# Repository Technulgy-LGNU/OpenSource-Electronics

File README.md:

# Technulgy Open-Source Electronics

This repository contains circuits and borads of our robots. There is one folder for each released version.
Mechanics are designed with Autodesk EAGLE.

Autodesk EAGLE is available for free for students.

Please check subfolders for further information on each version.

## Electronics Assembly Team Faabs 2025

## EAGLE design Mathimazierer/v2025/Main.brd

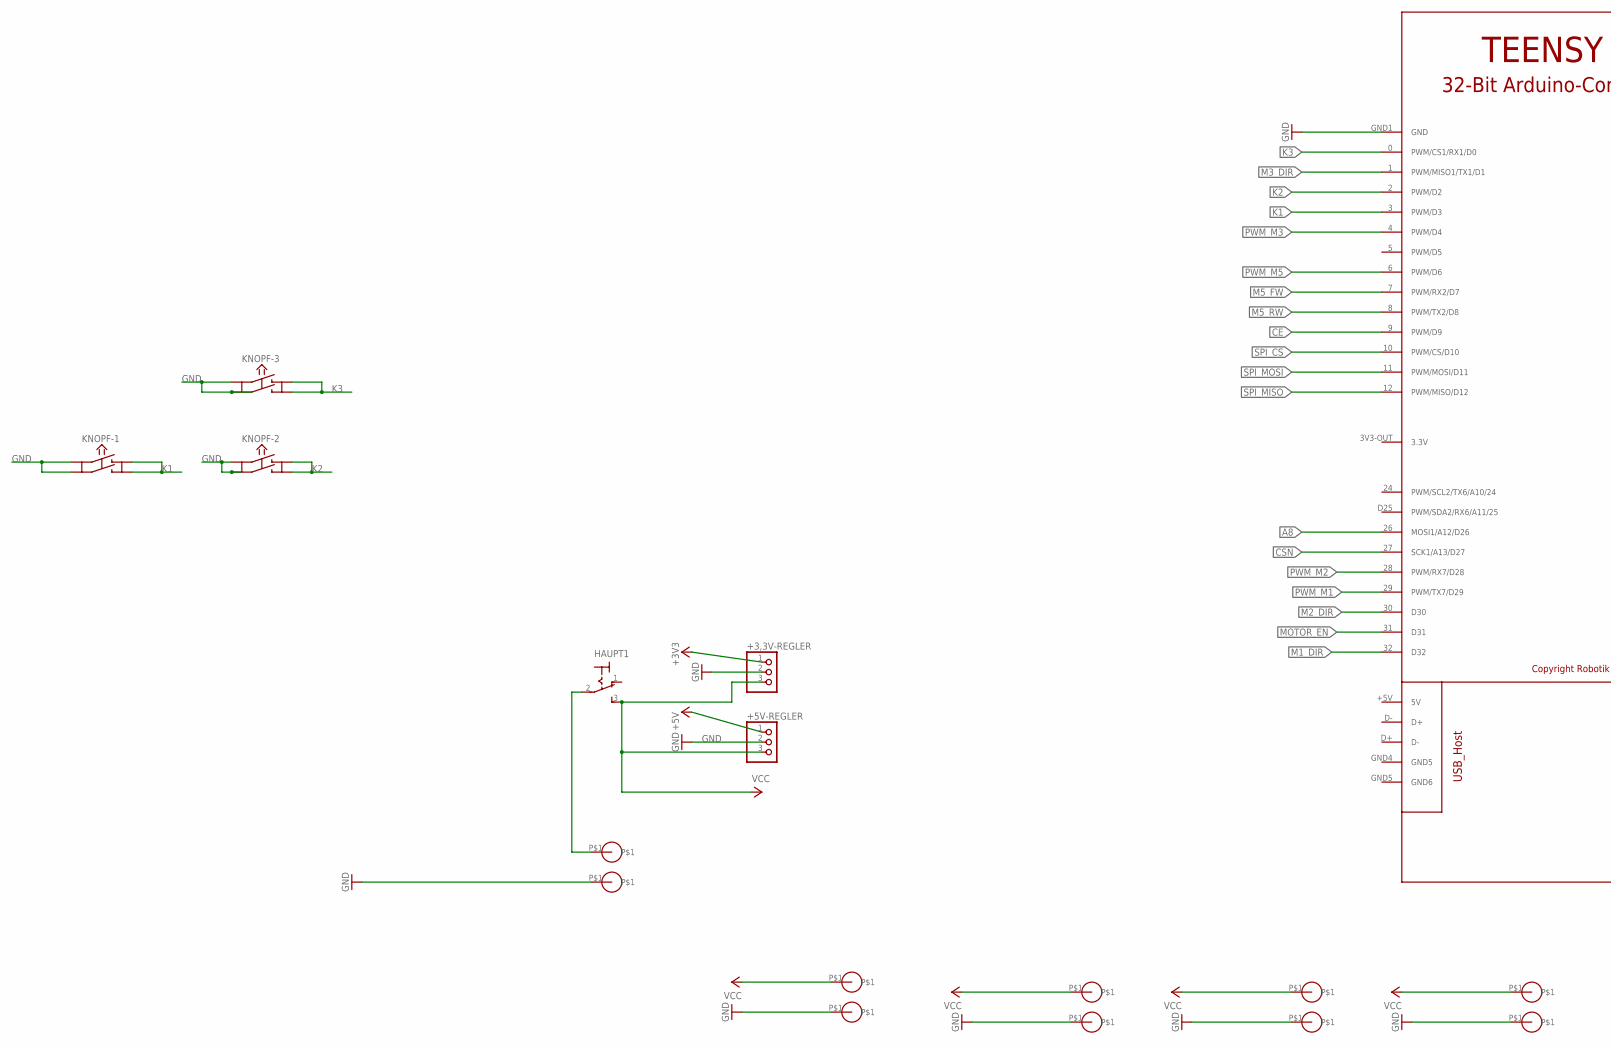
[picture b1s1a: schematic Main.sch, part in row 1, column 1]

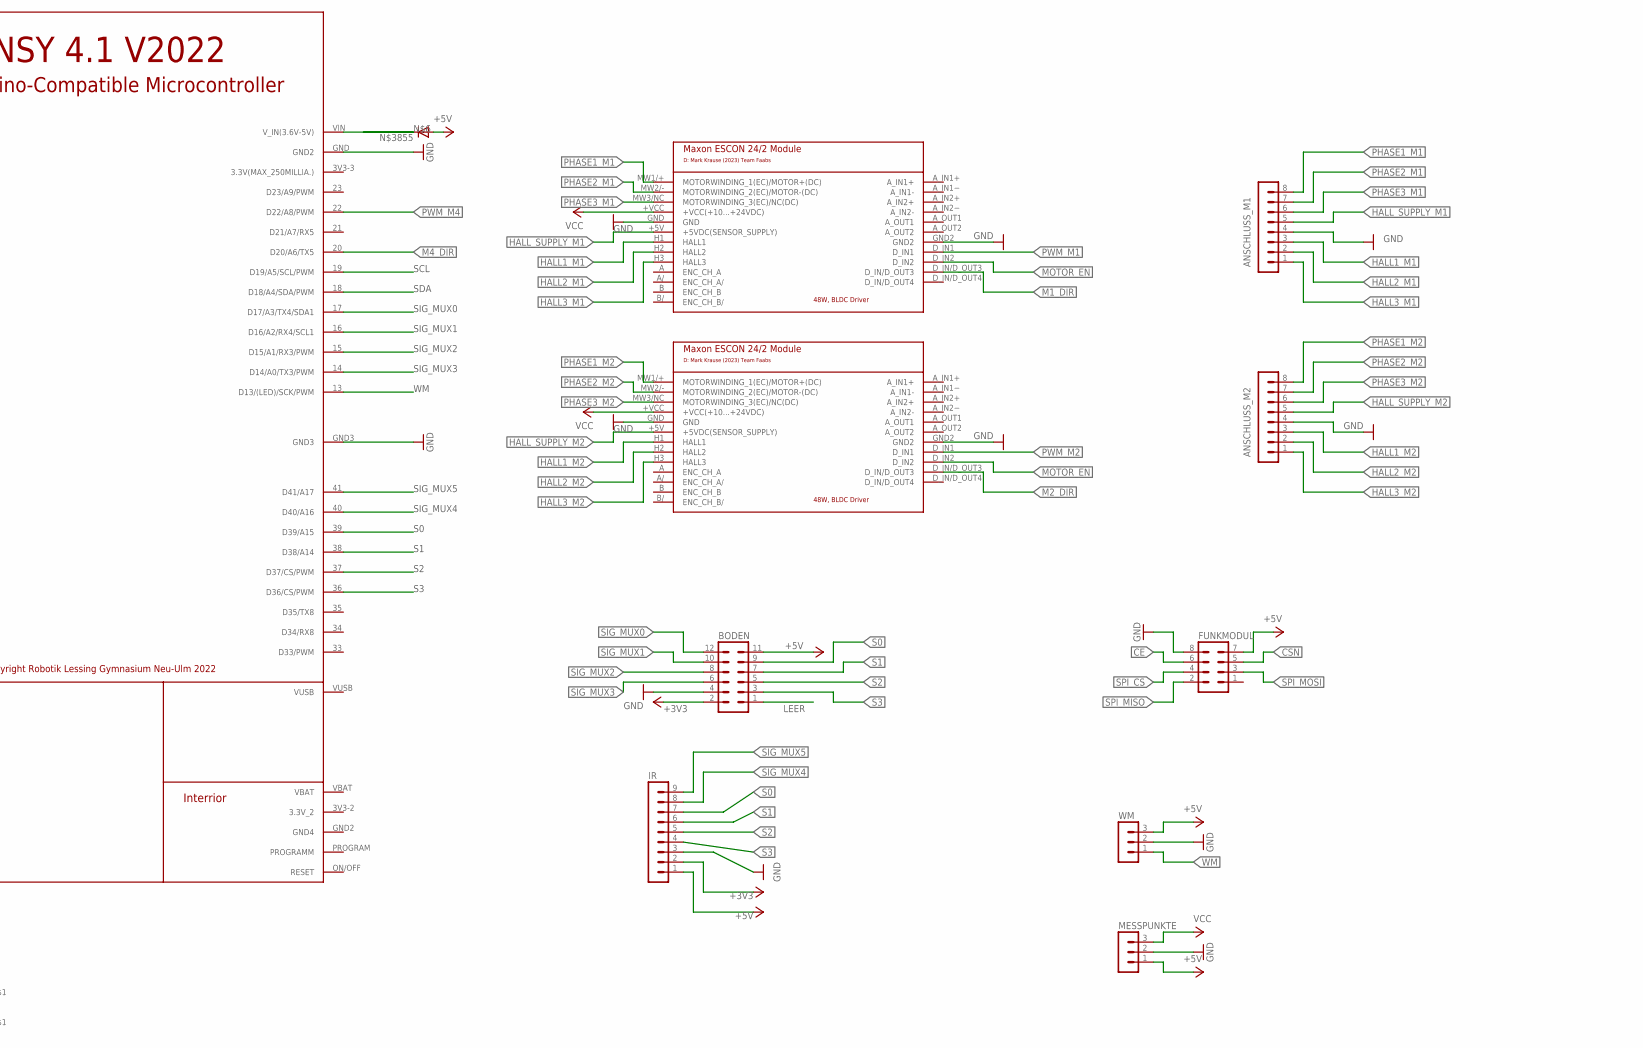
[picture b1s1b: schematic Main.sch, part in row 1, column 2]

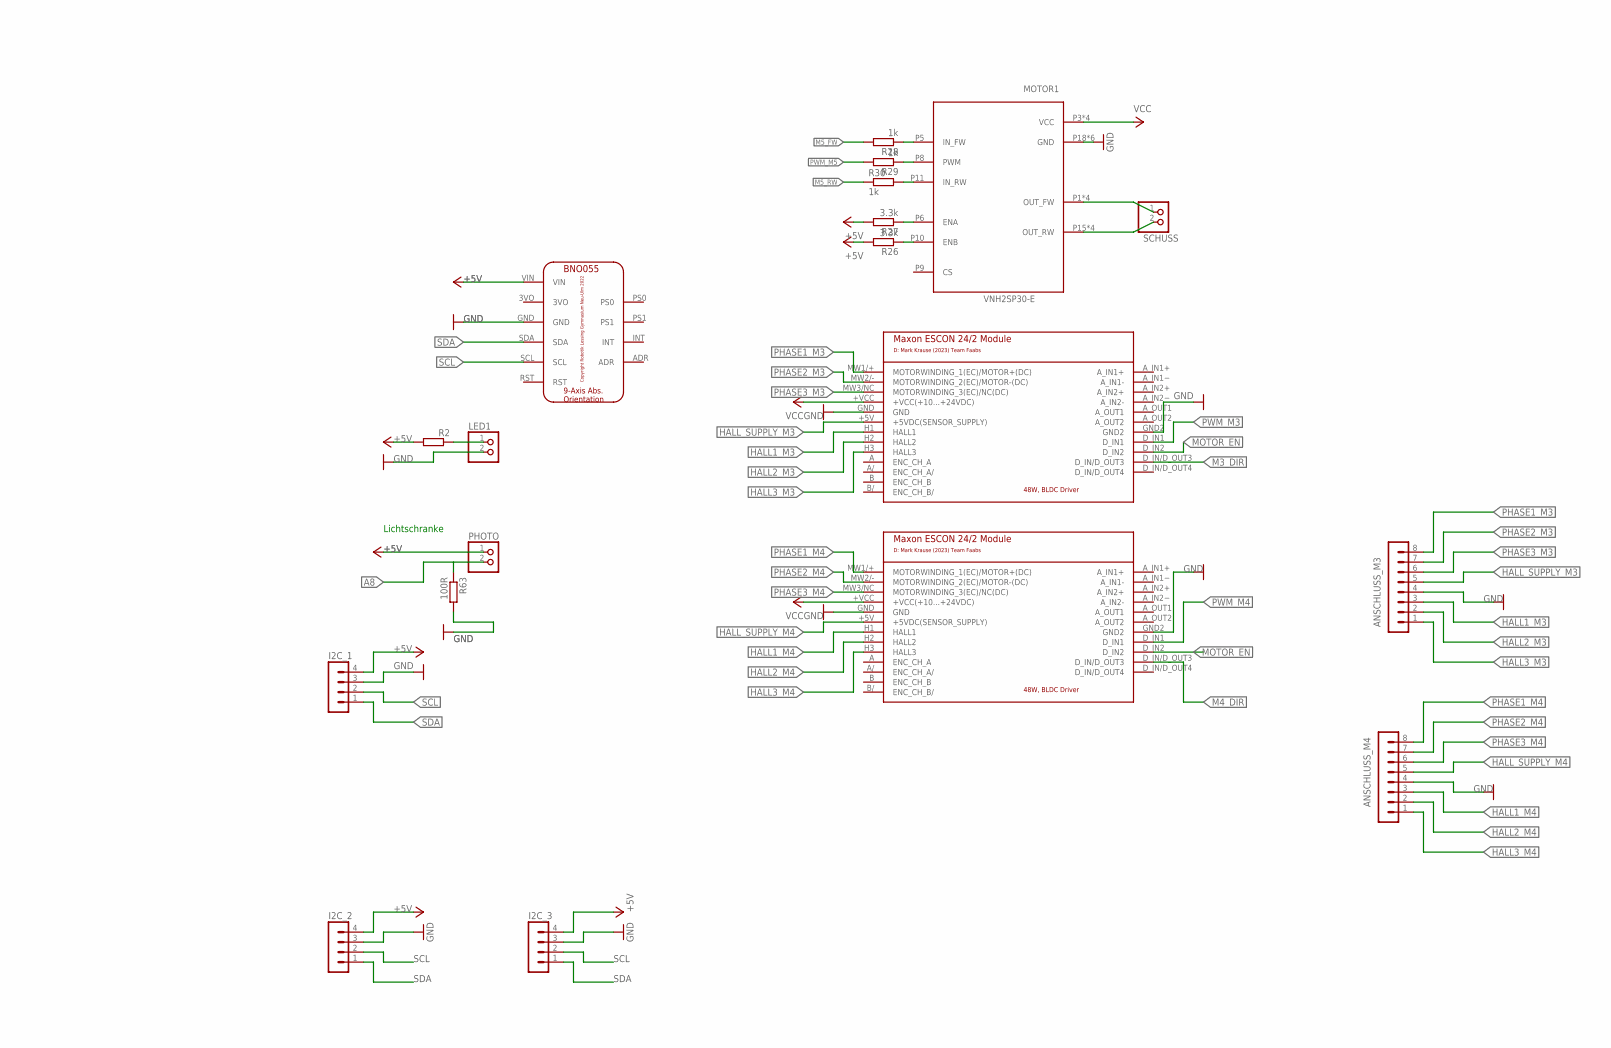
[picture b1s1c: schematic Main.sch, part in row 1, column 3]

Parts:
+3,3V-REGLER, +5V-REGLER: PINHD-1X3; 1X03
ANSCHLUSS_M1, ANSCHLUSS_M2, ANSCHLUSS_M3, ANSCHLUSS_M4: MA08-1
BNO055: BNO055
BODEN: MA06-2
FUNKMODUL: MA04-2
GND, GND10, GND11, GND35, GND37: PPAD
HAUPT1: 320-916
I2C_1, I2C_2, I2C_3: MA04-1
IR: MA09-1
KNOPF-1, KNOPF-2, KNOPF-3: KSM611A
LED1: PINHD-1X2; 1X02
MAIN, MAIN1, MAIN2, MAIN3, MAIN4: PPAD
MESSPUNKTE: MA03-1
MOTOR1: VNH2SP30-E; MP-SO-30
N$3855: DIODE-SMB; SMB
PHOTO: PINHD-1X2; 1X02
R2: 100R; R1206
R26, R27: 3.3k; R0805
R28, R29, R30: 1k; R0805
R63: 100R; R0805
SCHUSS: PINHD-1X2; 1X02
U$1, U$3, U$4, U$5: MAXON_ESCON24/2; MAXON_ESCON24/2_MODULE
U$2: TEENSY_4.1
WM: MA03-1

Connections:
+3V3: +3,3V-REGLER.1, BODEN.2, IR.2
+5V: +5V-REGLER.1, BNO055.VIN, BODEN.11, FUNKMODUL.7, I2C_1.4, I2C_2.4, I2C_3.4, IR.1, MESSPUNKTE.1, N$3855.A, PHOTO.1, R2.2, R26.2, R27.2, WM.3
A8: PHOTO.2, R63.1, U$2.26 (MOSI1/A12/D26)
CE: FUNKMODUL.6, U$2.9 (PWM/D9)
CSN: FUNKMODUL.5, U$2.27 (SCK1/A13/D27)
GND: +3,3V-REGLER.2, +5V-REGLER.2, ANSCHLUSS_M1.4, ANSCHLUSS_M2.4, ANSCHLUSS_M3.4, ANSCHLUSS_M4.4, BNO055.GND, BODEN.4, FUNKMODUL.8, GND.P$1, GND10.P$1, GND11.P$1, GND35.P$1, GND37.P$1, I2C_1.3, I2C_2.3, I2C_3.3, IR.3, KNOPF-1.A, KNOPF-1.C, KNOPF-2.A, KNOPF-2.C, KNOPF-3.A, KNOPF-3.C, LED1.2, MESSPUNKTE.2, MOTOR1.P18 (GND), MOTOR1.P19 (GND), MOTOR1.P20 (GND), MOTOR1.P26 (GND), MOTOR1.P27 (GND), MOTOR1.P28 (GND), R63.2, U$1.GND, U$1.GND2, U$2.GND (GND2), U$2.GND1 (GND), U$2.GND3, U$3.GND, U$3.GND2, U$4.GND, U$4.GND2, U$5.GND, U$5.GND2, WM.2
HALL1_M1: ANSCHLUSS_M1.3, U$1.H1 (HALL1)
HALL1_M2: ANSCHLUSS_M2.3, U$3.H1 (HALL1)
HALL1_M3: ANSCHLUSS_M3.3, U$4.H1 (HALL1)
HALL1_M4: ANSCHLUSS_M4.3, U$5.H1 (HALL1)
HALL2_M1: ANSCHLUSS_M1.2, U$1.H2 (HALL2)
HALL2_M2: ANSCHLUSS_M2.2, U$3.H2 (HALL2)
HALL2_M3: ANSCHLUSS_M3.2, U$4.H2 (HALL2)
HALL2_M4: ANSCHLUSS_M4.2, U$5.H2 (HALL2)
HALL3_M1: ANSCHLUSS_M1.1, U$1.H3 (HALL3)
HALL3_M2: ANSCHLUSS_M2.1, U$3.H3 (HALL3)
HALL3_M3: ANSCHLUSS_M3.1, U$4.H3 (HALL3)
HALL3_M4: ANSCHLUSS_M4.1, U$5.H3 (HALL3)
HALL_SUPPLY_M1: ANSCHLUSS_M1.5, U$1.+5V (+5VDC(SENSOR_SUPPLY))
HALL_SUPPLY_M2: ANSCHLUSS_M2.5, U$3.+5V (+5VDC(SENSOR_SUPPLY))
HALL_SUPPLY_M3: ANSCHLUSS_M3.5, U$4.+5V (+5VDC(SENSOR_SUPPLY))
HALL_SUPPLY_M4: ANSCHLUSS_M4.5, U$5.+5V (+5VDC(SENSOR_SUPPLY))
K1: KNOPF-1.B, KNOPF-1.D, U$2.3 (PWM/D3)
K2: KNOPF-2.B, KNOPF-2.D, U$2.2 (PWM/D2)
K3: KNOPF-3.B, KNOPF-3.D, U$2.0 (PWM/CS1/RX1/D0)
LEER: BODEN.1
M1_DIR: U$1.D_IN/D_OUT3, U$2.32 (D32)
M2_DIR: U$2.30 (D30), U$3.D_IN/D_OUT3
M3_DIR: U$2.1 (PWM/MISO1/TX1/D1), U$4.D_IN/D_OUT3
M4_DIR: U$2.20 (D20/A6/TX5), U$5.D_IN/D_OUT3
M5_FW: R28.2, U$2.7 (PWM/RX2/D7)
M5_RW: R30.1, U$2.8 (PWM/TX2/D8)
MOTOR_EN: U$1.D_IN2, U$2.31 (D31), U$3.D_IN2, U$4.D_IN2, U$5.D_IN2
unnamed: HAUPT1.2, MAIN.P$1
unnamed: LED1.1, R2.1
unnamed: N$3855.C, U$2.VIN (V_IN(3.6V-5V))
unnamed: MOTOR1.P5 (IN_FW), R28.1
unnamed: MOTOR1.P6 (ENA), R27.1
unnamed: MOTOR1.P10 (ENB), R26.1
unnamed: MOTOR1.P8 (PWM), R29.1
unnamed: MOTOR1.P11 (IN_RW), R30.2
unnamed: MOTOR1.P1 (OUT_FW), MOTOR1.P25 (OUT_FW), MOTOR1.P30 (OUT_FW), MOTOR1.S2 (OUT_FW), SCHUSS.1
unnamed: MOTOR1.P15 (OUT_RW), MOTOR1.P16 (OUT_RW), MOTOR1.P21 (OUT_RW), MOTOR1.S3 (OUT_RW), SCHUSS.2
PHASE1_M1: ANSCHLUSS_M1.8, U$1.MW1/+ (MOTORWINDING_1(EC)/MOTOR+(DC))
PHASE1_M2: ANSCHLUSS_M2.8, U$3.MW1/+ (MOTORWINDING_1(EC)/MOTOR+(DC))
PHASE1_M3: ANSCHLUSS_M3.8, U$4.MW1/+ (MOTORWINDING_1(EC)/MOTOR+(DC))
PHASE1_M4: ANSCHLUSS_M4.8, U$5.MW1/+ (MOTORWINDING_1(EC)/MOTOR+(DC))
PHASE2_M1: ANSCHLUSS_M1.7, U$1.MW2/- (MOTORWINDING_2(EC)/MOTOR-(DC))
PHASE2_M2: ANSCHLUSS_M2.7, U$3.MW2/- (MOTORWINDING_2(EC)/MOTOR-(DC))
PHASE2_M3: ANSCHLUSS_M3.7, U$4.MW2/- (MOTORWINDING_2(EC)/MOTOR-(DC))
PHASE2_M4: ANSCHLUSS_M4.7, U$5.MW2/- (MOTORWINDING_2(EC)/MOTOR-(DC))
PHASE3_M1: ANSCHLUSS_M1.6, U$1.MW3/NC (MOTORWINDING_3(EC)/NC(DC))
PHASE3_M2: ANSCHLUSS_M2.6, U$3.MW3/NC (MOTORWINDING_3(EC)/NC(DC))
PHASE3_M3: ANSCHLUSS_M3.6, U$4.MW3/NC (MOTORWINDING_3(EC)/NC(DC))
PHASE3_M4: ANSCHLUSS_M4.6, U$5.MW3/NC (MOTORWINDING_3(EC)/NC(DC))
PWM_M1: U$1.D_IN1, U$2.29 (PWM/TX7/D29)
PWM_M2: U$2.28 (PWM/RX7/D28), U$3.D_IN1
PWM_M3: U$2.4 (PWM/D4), U$4.D_IN1
PWM_M4: U$2.22 (D22/A8/PWM), U$5.D_IN1
PWM_M5: R29.2, U$2.6 (PWM/D6)
S0: BODEN.9, IR.7, U$2.39 (D39/A15)
S1: BODEN.7, IR.6, U$2.38 (D38/A14)
S2: BODEN.5, IR.5, U$2.37 (D37/CS/PWM)
S3: BODEN.3, IR.4, U$2.36 (D36/CS/PWM)
SCL: BNO055.SCL, I2C_1.2, I2C_2.2, I2C_3.2, U$2.19 (D19/A5/SCL/PWM)
SDA: BNO055.SDA, I2C_1.1, I2C_2.1, I2C_3.1, U$2.18 (D18/A4/SDA/PWM)
SIG_MUX0: BODEN.12, U$2.17 (D17/A3/TX4/SDA1)
SIG_MUX1: BODEN.10, U$2.16 (D16/A2/RX4/SCL1)
SIG_MUX2: BODEN.8, U$2.15 (D15/A1/RX3/PWM)
SIG_MUX3: BODEN.6, U$2.14 (D14/A0/TX3/PWM)
SIG_MUX4: IR.8, U$2.40 (D40/A16)
SIG_MUX5: IR.9, U$2.41 (D41/A17)
SPI_CS: FUNKMODUL.4, U$2.10 (PWM/CS/D10)
SPI_MISO: FUNKMODUL.2, U$2.12 (PWM/MISO/D12)
SPI_MOSI: FUNKMODUL.3, U$2.11 (PWM/MOSI/D11)
VCC: +3,3V-REGLER.3, +5V-REGLER.3, HAUPT1.3 (S), MAIN1.P$1, MAIN2.P$1, MAIN3.P$1, MAIN4.P$1, MESSPUNKTE.3, MOTOR1.P3 (VCC), MOTOR1.P13 (VCC), MOTOR1.P23 (VCC), MOTOR1.S1 (VCC), U$1.+VCC (+VCC(+10...+24VDC)), U$3.+VCC (+VCC(+10...+24VDC)), U$4.+VCC (+VCC(+10...+24VDC)), U$5.+VCC (+VCC(+10...+24VDC))
WM: U$2.13 (D13/(LED)/SCK/PWM), WM.1

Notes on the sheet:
Lichtschranke

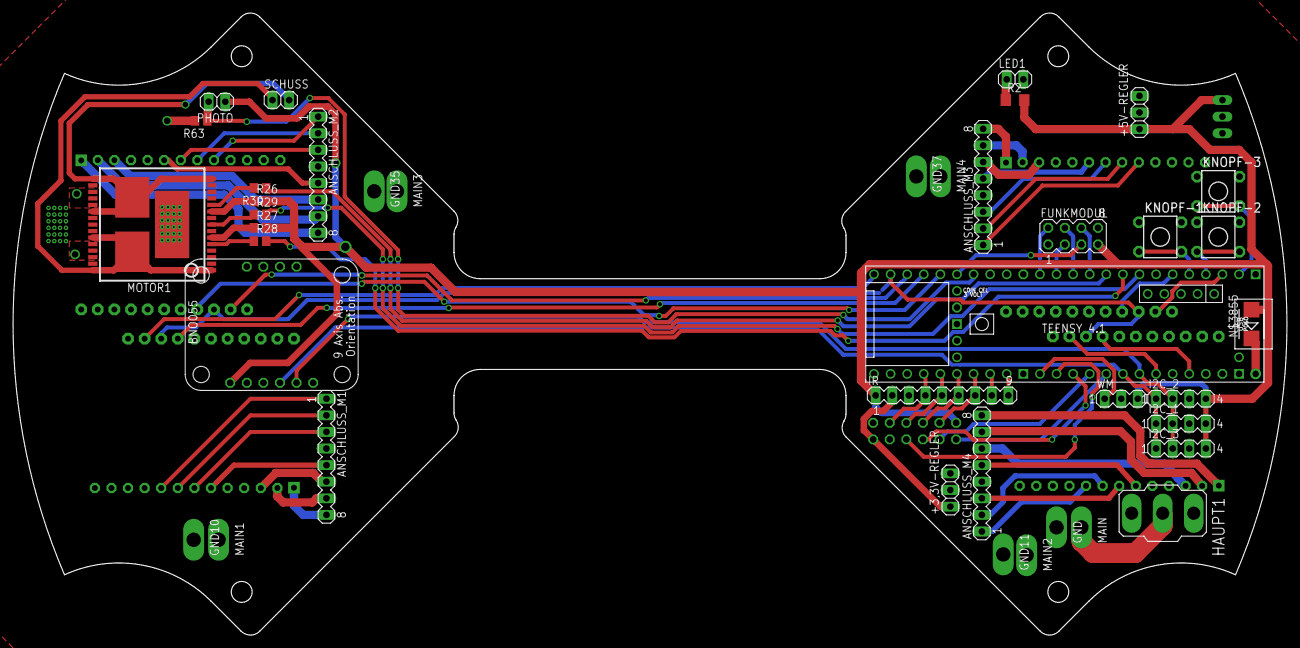
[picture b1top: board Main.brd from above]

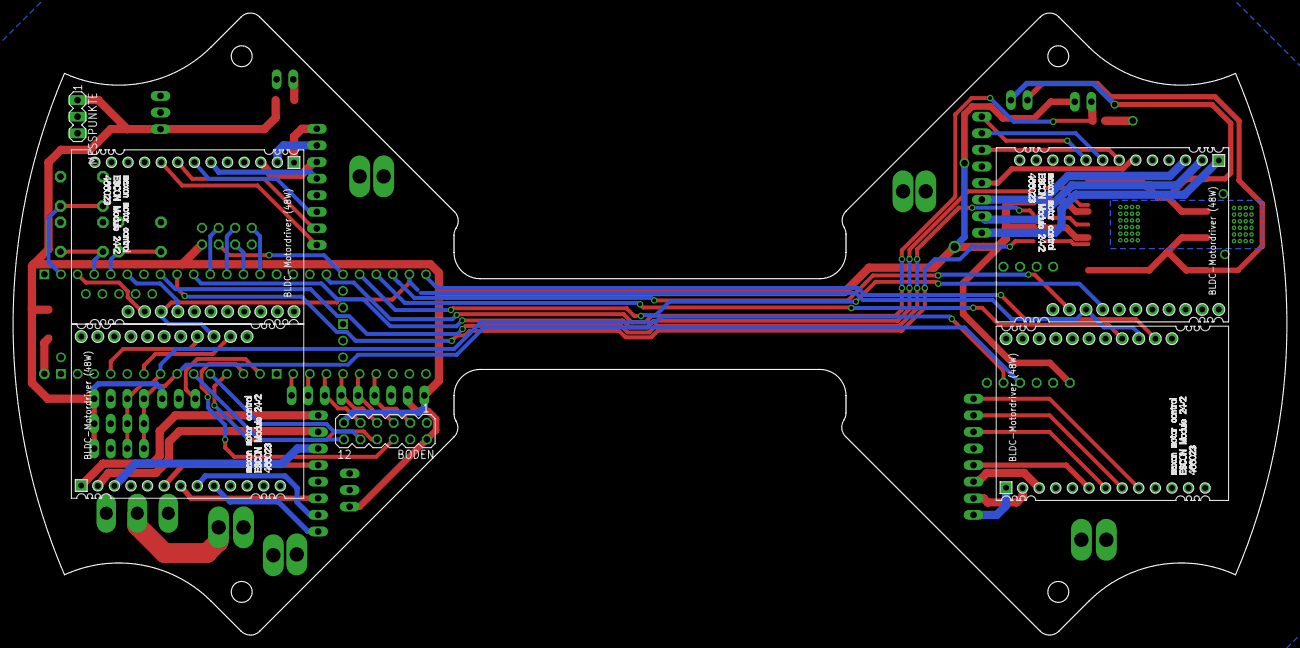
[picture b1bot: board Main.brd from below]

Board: 2 copper layers, 195.0 x 95.2 mm, 46 parts (6 on the bottom side), 76 nets.

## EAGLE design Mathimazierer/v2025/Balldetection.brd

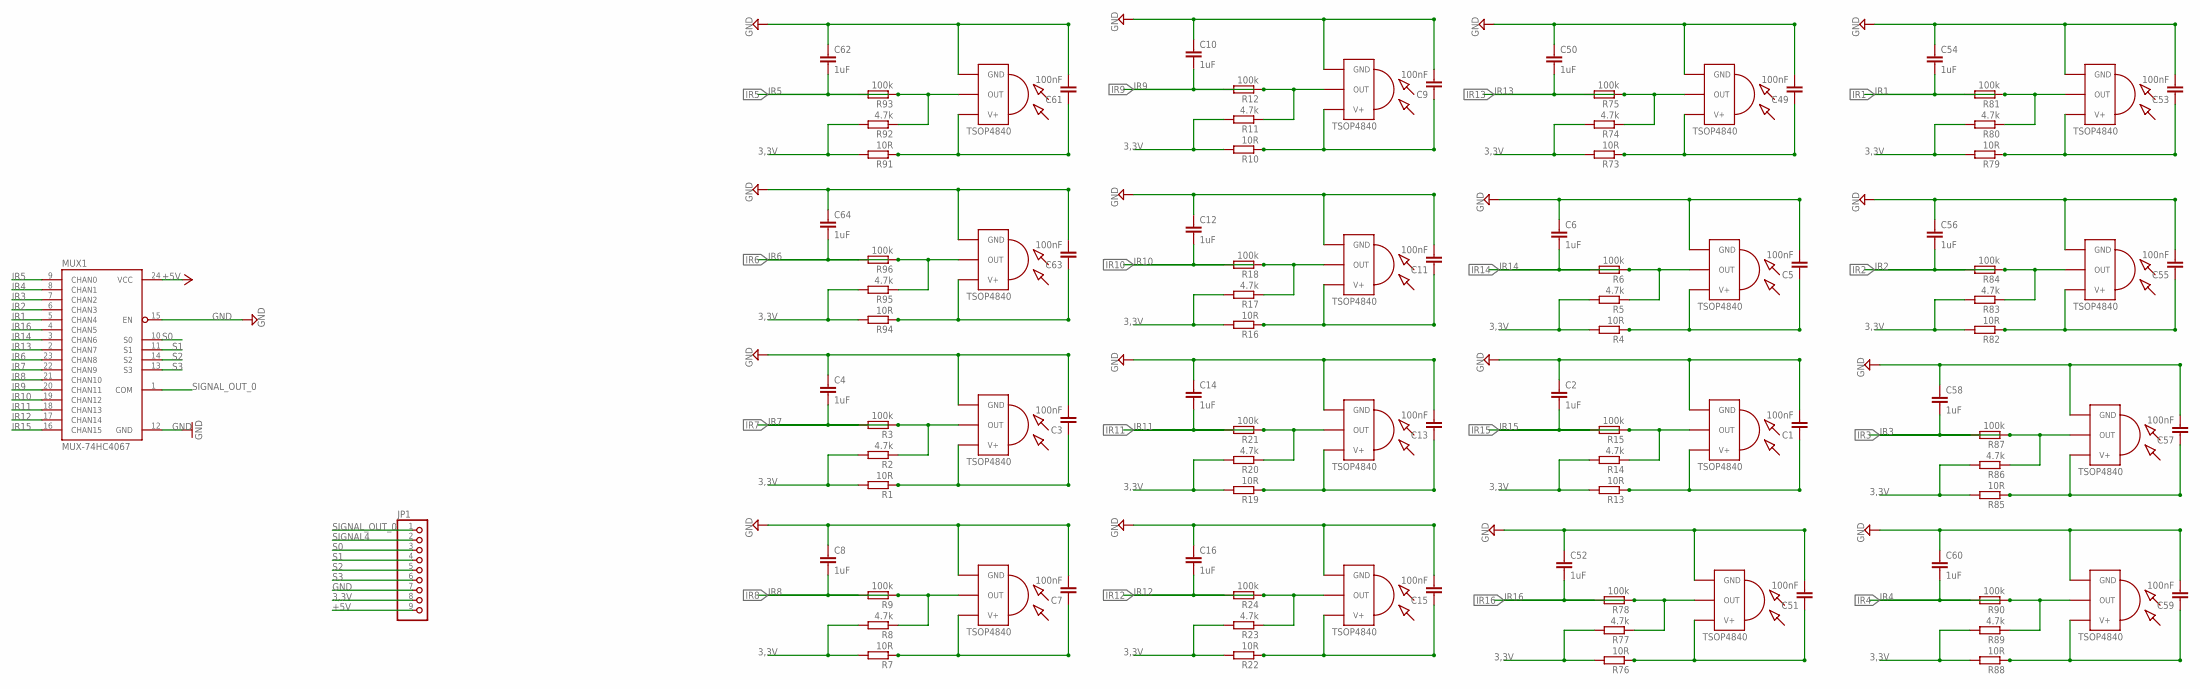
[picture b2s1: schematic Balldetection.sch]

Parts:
C1, C3, C5, C7, C9, C11, C13, C15, C49, C51, C53, C55, C57, C59, C61, C63: 100nF; C1206
C2, C4, C6, C8, C10, C12, C14, C16, C50, C52, C54, C56, C58, C60, C62, C64: 1uF; C1206
IR1, IR2, IR3, IR4, IR5, IR6, IR7, IR8, IR9, IR10, IR11, IR12, IR13, IR14, IR15, IR16: TSOP4840; TSOP18XX
JP1: PINHD-1X9; 1X09
MUX1: MUX-74HC4067; SSOP24
R1, R4, R7, R10, R13, R16, R19, R22, R73, R76, R79, R82, R85, R88, R91, R94: 10R; R1206
R2, R5, R8, R11, R14, R17, R20, R23, R74, R77, R80, R83, R86, R89, R92, R95: 4.7k; R1206
R3, R6, R9, R12, R15, R18, R21, R24, R75, R78, R81, R84, R87, R90, R93, R96: 100k; R1206

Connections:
3,3V: JP1.8, R1.2, R2.2, R4.2, R5.2, R7.2, R8.2, R10.2, R11.2, R13.2, R14.2, R16.2, R17.2, R19.2, R20.2, R22.2, R23.2, R73.2, R74.2, R76.2, R77.2, R79.2, R80.2, R82.2, R83.2, R85.2, R86.2, R88.2, R89.2, R91.2, R92.2, R94.2, R95.2
+5V: JP1.9, MUX1.24 (VCC)
GND: C1.2, C2.1, C3.2, C4.1, C5.2, C6.1, C7.2, C8.1, C9.2, C10.1, C11.2, C12.1, C13.2, C14.1, C15.2, C16.1, C49.2, C50.1, C51.2, C52.1, C53.2, C54.1, C55.2, C56.1, C57.2, C58.1, C59.2, C60.1, C61.2, C62.1, C63.2, C64.1, IR1.GND, IR2.GND, IR3.GND, IR4.GND, IR5.GND, IR6.GND, IR7.GND, IR8.GND, IR9.GND, IR10.GND, IR11.GND, IR12.GND, IR13.GND, IR14.GND, IR15.GND, IR16.GND, JP1.7, MUX1.12 (GND), MUX1.15 (EN)
IR1: C54.2, MUX1.5 (CHAN4), R81.2
IR2: C56.2, MUX1.6 (CHAN3), R84.2
IR3: C58.2, MUX1.7 (CHAN2), R87.2
IR4: C60.2, MUX1.8 (CHAN1), R90.2
IR5: C62.2, MUX1.9 (CHAN0), R93.2
IR6: C64.2, MUX1.23 (CHAN8), R96.2
IR7: C4.2, MUX1.22 (CHAN9), R3.2
IR8: C8.2, MUX1.21 (CHAN10), R9.2
IR9: C10.2, MUX1.20 (CHAN11), R12.2
IR10: C12.2, MUX1.19 (CHAN12), R18.2
IR11: C14.2, MUX1.18 (CHAN13), R21.2
IR12: C16.2, MUX1.17 (CHAN14), R24.2
IR13: C50.2, MUX1.2 (CHAN7), R75.2
IR14: C6.2, MUX1.3 (CHAN6), R6.2
IR15: C2.2, MUX1.16 (CHAN15), R15.2
IR16: C52.2, MUX1.4 (CHAN5), R78.2
unnamed: C3.1, IR15.VCC (V+), R1.1
unnamed: IR15.OUT, R2.1, R3.1
unnamed: C5.1, IR8.VCC (V+), R4.1
unnamed: IR8.OUT, R5.1, R6.1
unnamed: C7.1, IR14.VCC (V+), R7.1
unnamed: C1.1, IR7.VCC (V+), R13.1
unnamed: IR14.OUT, R8.1, R9.1
unnamed: C9.1, IR13.VCC (V+), R10.1
unnamed: IR13.OUT, R11.1, R12.1
unnamed: C11.1, IR12.VCC (V+), R16.1
unnamed: IR12.OUT, R17.1, R18.1
unnamed: C13.1, IR11.VCC (V+), R19.1
unnamed: IR11.OUT, R20.1, R21.1
unnamed: C15.1, IR10.VCC (V+), R22.1
unnamed: IR10.OUT, R23.1, R24.1
unnamed: IR7.OUT, R14.1, R15.1
unnamed: C49.1, IR9.VCC (V+), R73.1
unnamed: IR9.OUT, R74.1, R75.1
unnamed: C51.1, IR6.VCC (V+), R76.1
unnamed: IR6.OUT, R77.1, R78.1
unnamed: C53.1, IR5.VCC (V+), R79.1
unnamed: IR5.OUT, R80.1, R81.1
unnamed: C55.1, IR4.VCC (V+), R82.1
unnamed: IR4.OUT, R83.1, R84.1
unnamed: C57.1, IR3.VCC (V+), R85.1
unnamed: IR3.OUT, R86.1, R87.1
unnamed: C59.1, IR2.VCC (V+), R88.1
unnamed: IR2.OUT, R89.1, R90.1
unnamed: C61.1, IR1.VCC (V+), R91.1
unnamed: IR1.OUT, R92.1, R93.1
unnamed: C63.1, IR16.VCC (V+), R94.1
unnamed: IR16.OUT, R95.1, R96.1
S0: JP1.3, MUX1.10 (S0)
S1: JP1.4, MUX1.11 (S1)
S2: JP1.5, MUX1.14 (S2)
S3: JP1.6, MUX1.13 (S3)
SIGNAL4: JP1.2
SIGNAL_OUT_0: JP1.1, MUX1.1 (COM)

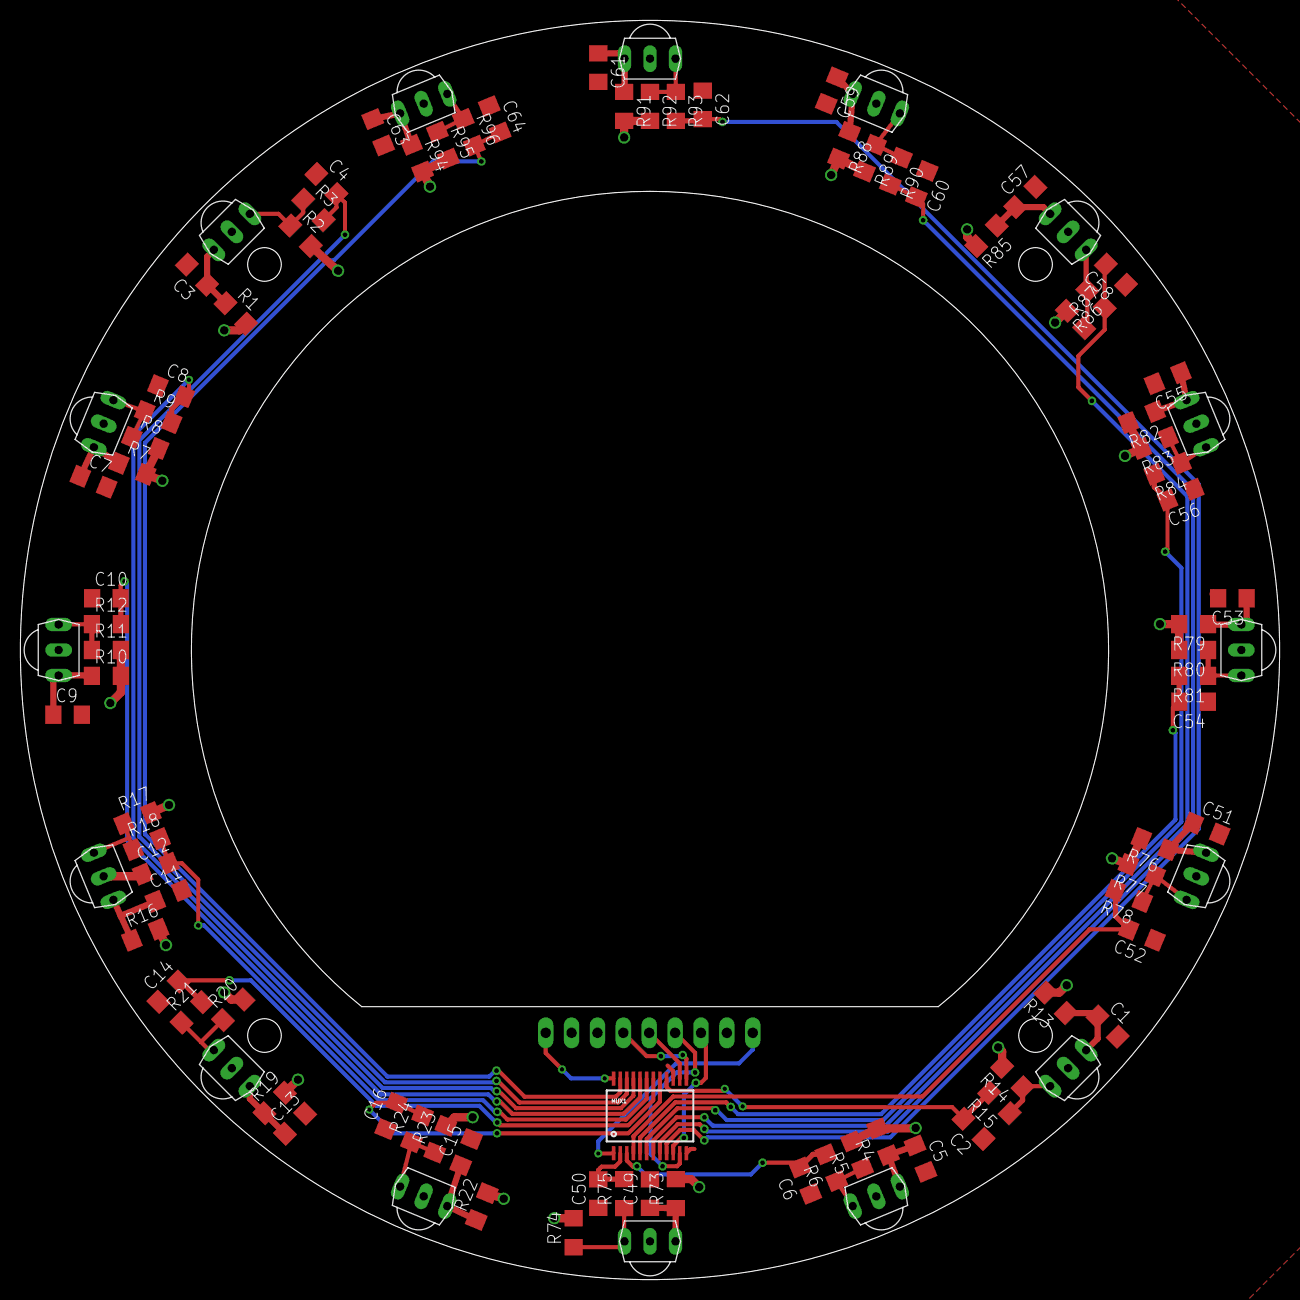
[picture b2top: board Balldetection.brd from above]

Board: 2 copper layers, 123.6 x 123.6 mm, 98 parts (1 on the bottom side), 56 nets.

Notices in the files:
parts and their libraries:
Teensy41: Copyright Robotik Lessing Gymnasium Neu-Ulm 2022
rc-master-smd: Copyright (C) 2007, Bob Starr
